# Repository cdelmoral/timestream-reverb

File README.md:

# Timestream Reverb Guitar Pedal

This project contains the kicad files for the Timestream Reverb guitar pedal, designed by
[DEADASTRONAUTFX](https://deadastronaut.wixsite.com/effects/timestreamreverb) (thank you!).

## Requirements

In order to open the project you will need to have [kicad](https://www.kicad.org/) installed
in your computer.

## Bill of Materials

| Designator         | Designation                           | Quantity |
| ------------------ | ------------------------------------- | -------- |
| C1,C5              | 10uF                                  | 2        |
| C2,C3,C4           | 100uF                                 | 3        |
| C6                 | 100nF                                 | 1        |
| C7,C9              | 22nF                                  | 2        |
| C8                 | 100pF                                 | 1        |
| C10                | 4.7nF                                 | 1        |
| C11                | 33nF                                  | 1        |
| C12                | 1uF                                   | 1        |
| D2                 | 1N5817                                | 1        |
| R1                 | 330Ω                                  | 1        |
| R2                 | 4.7kΩ                                 | 1        |
| R3                 | 33Ω                                   | 1        |
| R4,R5,R6,R7        | 1MΩ                                   | 4        |
| R8,R11,R12,R13,R15 | 10kΩ                                  | 5        |
| R9,R14             | 22kΩ                                  | 2        |
| R10                | 1kΩ                                   | 1        |
| RV1,RV3,RV4        | 10kb                                  | 3        |
| RV2                | 25kb                                  | 1        |
| U1                 | L78L05_TO92                           | 1        |
| U2,U3              | TL072                                 | 2        |
| U4                 | Accutronics Digi-Log Reverb (BTDR-2H) | 1        |
| LED                |                                       | 1        |
| Switch ON/ON       |                                       | 1        |
| Mono Jack          |                                       | 2        |
| 9V Jack            |                                       | 1        |
| 3PDT Switch        |                                       | 1        |

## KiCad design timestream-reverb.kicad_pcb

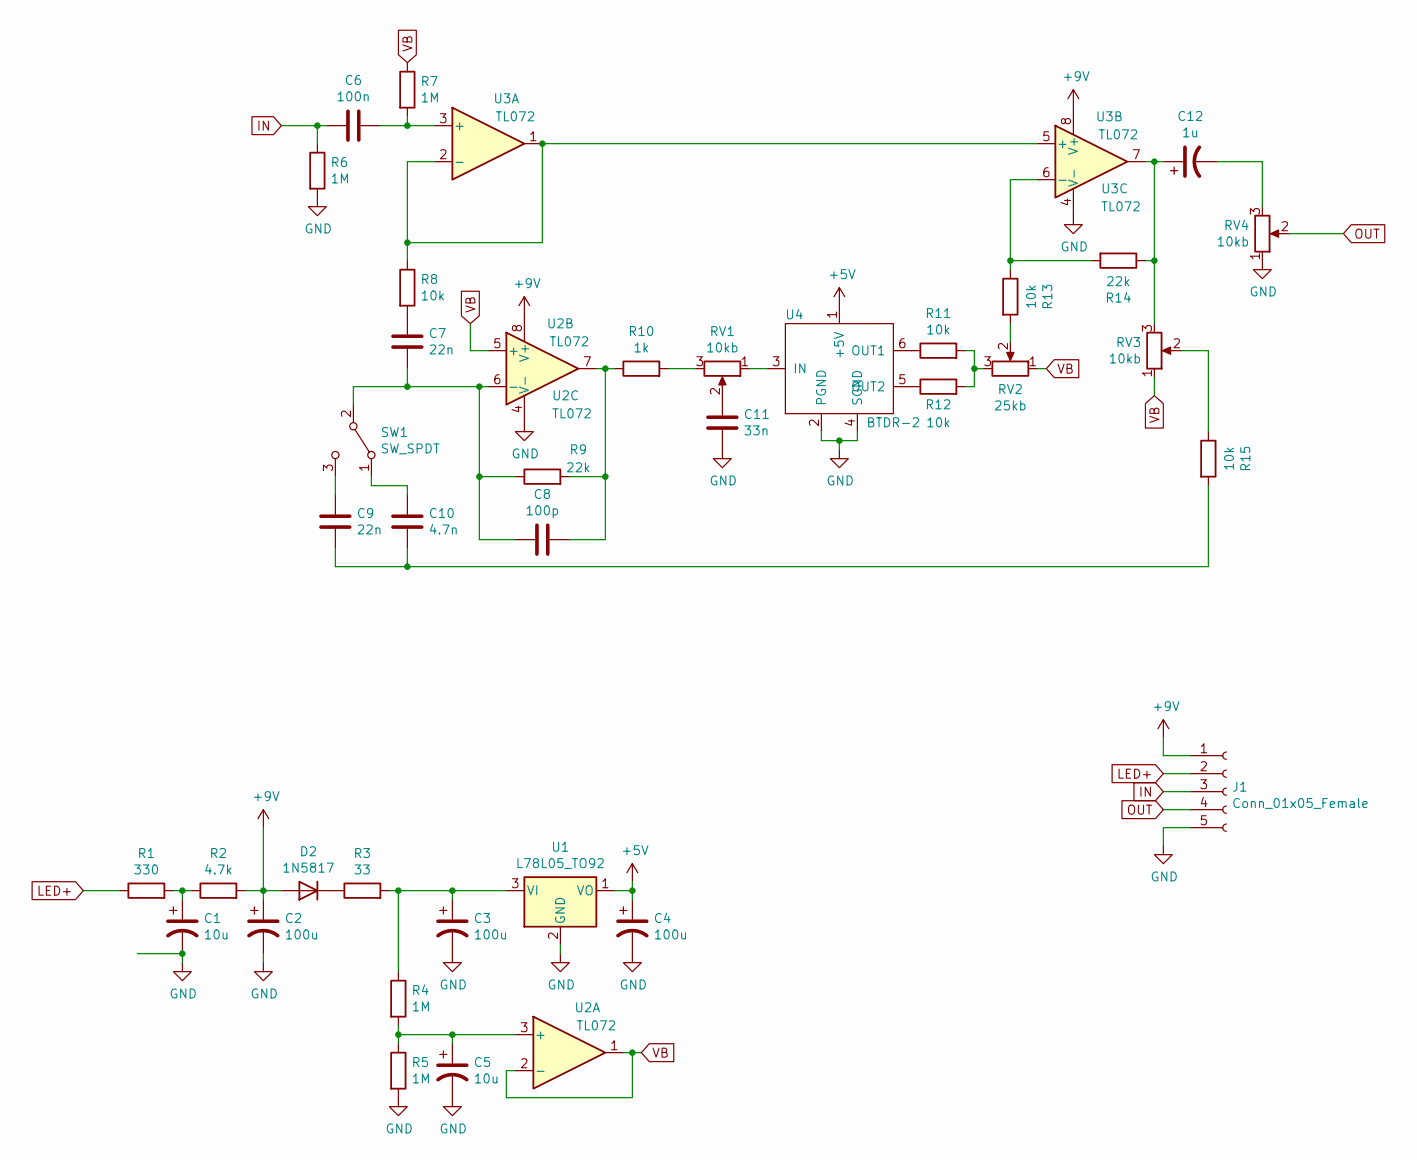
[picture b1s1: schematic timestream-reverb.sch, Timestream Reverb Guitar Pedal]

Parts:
C1, C5: 10u; CP_Radial_D5.0mm_P2.00mm
C2, C3, C4: 100u; CP_Radial_D5.0mm_P2.00mm
C6: 100n; C_Rect_L7.0mm_W2.5mm_P5.00mm
C7, C9: 22n; C_Rect_L7.0mm_W2.5mm_P5.00mm
C8: 100p; C_Disc_D3.0mm_W1.6mm_P2.50mm
C10: 4.7n; C_Rect_L7.0mm_W2.5mm_P5.00mm
C11: 33n; C_Rect_L7.0mm_W2.5mm_P5.00mm
C12: 1u; CP_Radial_D5.0mm_P2.00mm
D2: 1N5817; D_DO-41_SOD81_P7.62mm_Horizontal
J1: Conn_01x05_Female; TerminalBlock_5pin_2.54mm
R1: 330; R_Axial_DIN0207_L6.3mm_D2.5mm_P10.16mm_Horizontal
R2: 4.7k; R_Axial_DIN0207_L6.3mm_D2.5mm_P10.16mm_Horizontal
R3: 33; R_Axial_DIN0207_L6.3mm_D2.5mm_P10.16mm_Horizontal
R4, R5, R6, R7: 1M; R_Axial_DIN0207_L6.3mm_D2.5mm_P10.16mm_Horizontal
R8, R11, R12, R13, R15: 10k; R_Axial_DIN0207_L6.3mm_D2.5mm_P10.16mm_Horizontal
R9, R14: 22k; R_Axial_DIN0207_L6.3mm_D2.5mm_P10.16mm_Horizontal
R10: 1k; R_Axial_DIN0207_L6.3mm_D2.5mm_P10.16mm_Horizontal
RV1, RV3, RV4: 10kb; Tayda_Potentiometer
RV2: 25kb; Tayda_Potentiometer
SW1: SW_SPDT; TerminalBlock_3pin_2.54mm
U1: L78L05_TO92; TO-92_Inline
U2, U3: TL072; DIP-8_W7.62mm
U4: BTDR-2; TerminalBlock_6pin_2.54mm

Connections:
+5V: C4.1, U1.1 (VO), U4.1 (+5V)
+9V: C2.1, D2.2 (A), J1.1, R2.2, U2.8 (V+), U3.8 (V+)
GND: C1.2, C2.2, C3.2, C4.2, C5.2, C11.1, J1.5, R5.2, R6.2, RV4.1, U1.2 (GND), U2.4 (V-), U3.4 (V-), U4.2 (PGND), U4.4 (SGND)
IN: C6.2, J1.3, R6.1
LED+: J1.2, R1.1
unnamed: C1.1, R1.2, R2.1
unnamed: C3.1, R3.2, R4.1, U1.3 (VI)
unnamed: C5.1, R4.2, R5.1, U2.3 (+)
unnamed: C6.1, R7.2, U3.3 (+)
unnamed: C7.1, C8.1, R9.1, SW1.2 (B), U2.6 (-)
unnamed: C7.2, R8.2
unnamed: C8.2, R9.2, R10.1, U2.7
unnamed: C9.2, SW1.3 (C)
unnamed: C9.1, C10.1, R15.2
unnamed: C10.2, SW1.1 (A)
unnamed: C11.2, RV1.2
unnamed: C12.1, R14.1, RV3.3, U3.7
unnamed: C12.2, RV4.3
unnamed: D2.1 (K), R3.1
unnamed: R8.1, U3.1, U3.2 (-), U3.5 (+)
unnamed: R10.2, RV1.3
unnamed: R11.1, U4.6 (OUT1)
unnamed: R11.2, R12.2, RV2.3
unnamed: R12.1, U4.5 (OUT2)
unnamed: R13.1, R14.2, U3.6 (-)
unnamed: R13.2, RV2.2
unnamed: R15.1, RV3.2
unnamed: RV1.1, U4.3 (IN)
OUT: J1.4, RV4.2
VB: R7.1, RV2.1, RV3.1, U2.1, U2.2 (-), U2.5 (+)

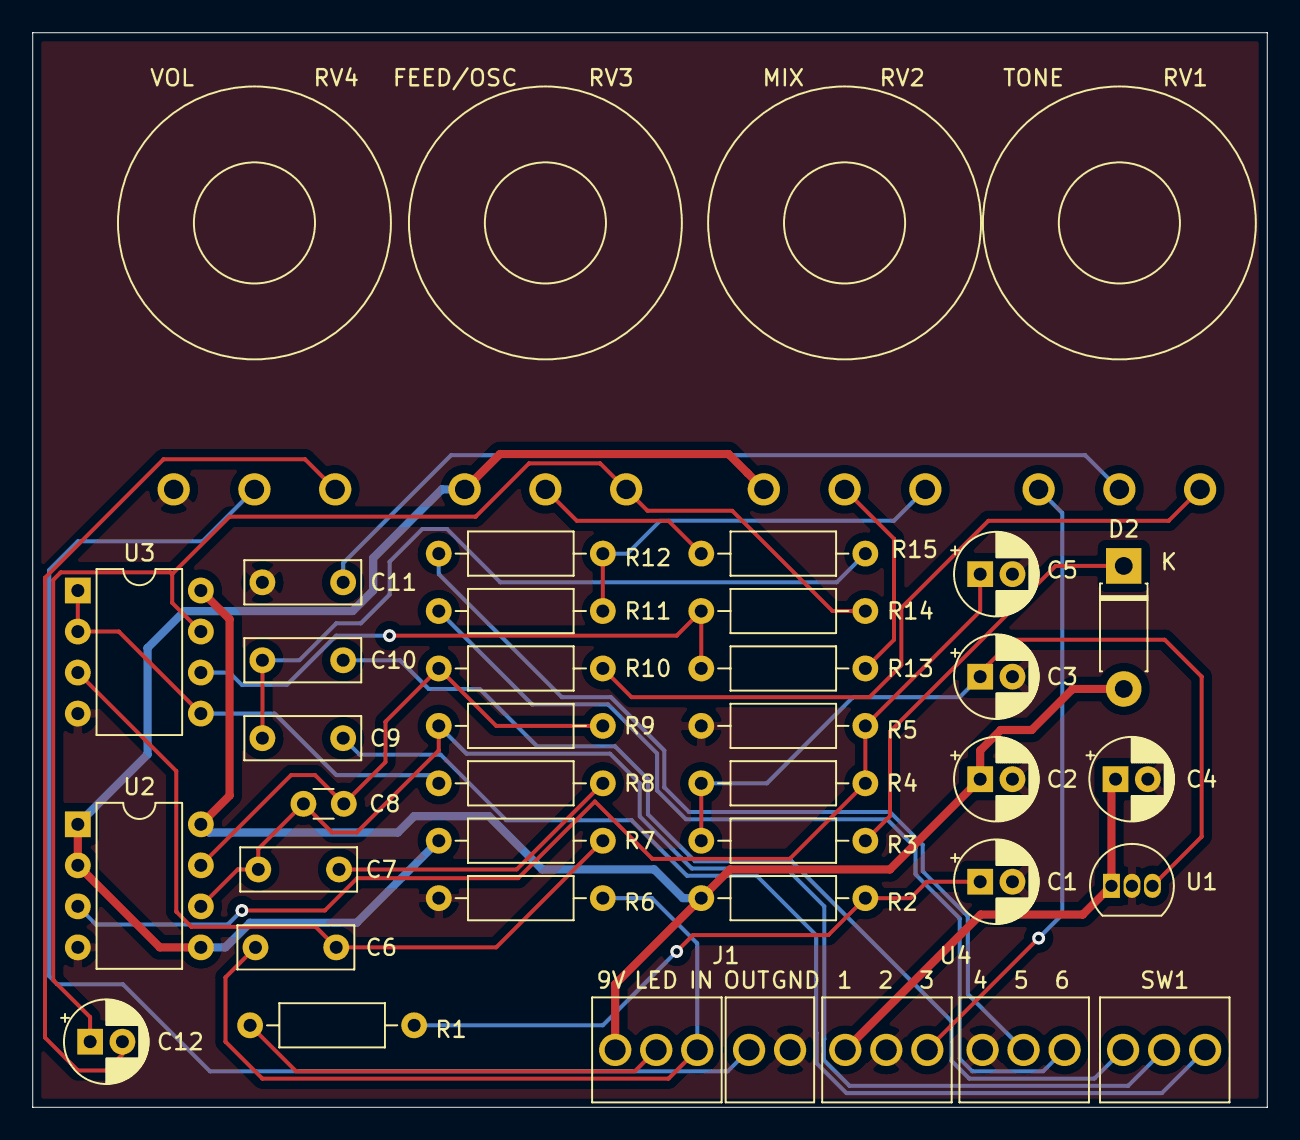
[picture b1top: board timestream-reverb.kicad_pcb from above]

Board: 2 copper layers, 76.5 x 66.5 mm, 38 parts (0 on the bottom side), 30 nets.

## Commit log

2022-01-26 Add project library with BTDR-2 symbol
2022-01-26 Create schematic
2022-01-26 Add README
2022-01-26 Make GND pins unspecified
2022-01-26 Annotate
2022-01-30 Finish PCB
2022-01-30 Add gitignore
2022-04-02 fix: Improve layout and remove wires to PCB
    The following has been fixed:
    - Wires are no longer wired to the PCB
    - PCB size is smaller
    - LED is not included in the layout
    - BTDR-2 is not included in the layout
2022-04-02 chore: Clean up ignored files
2022-04-02 docs: Add project description and bill of materials
2022-04-04 chore: Update options to generate gerber files
